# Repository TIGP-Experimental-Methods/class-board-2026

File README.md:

# class-board-2026

The teaching instrument for **Basic Skills for Experimentalists** (TIGP, 2026): one ESP32-S3 board (the ESP32-S3 is the microcontroller we use — a small computer on a chip, with WiFi) with three student-designed sections, a phone web app, and a Python client. The board is a small **NMR console**: a 2 mT field, a bottle of water, a pulse at 89 kHz, and the free induction decay that comes back turned into a spectrum on your phone.

| Folder | What | Who edits it |
|---|---|---|
| `hardware/` | KiCad project and library (KiCad is the free program we draw the schematic and lay out the printed circuit board in; the library is the set of symbols and footprints for our parts) | students in their zone (the region of the board that is theirs), instructor merges (brings their changes into the main line) |
| `firmware/` | PlatformIO project (Arduino, ESP32-S3) — the firmware is the program that runs on the microcontroller; PlatformIO is the tool that builds it and writes it onto the board | students, in the driver folders their instrument needs, under `src/blocks/` |
| `host/pwa/` | the phone app (plain HTML/JS, no build step) | students, in the panel files of those drivers, under `panels/` |
| `host/instrument.py` | Python command-line client (CLI) speaking the same protocol as the phone | instructor |

**The three sections of the board** (one design, made together in Workshop 2; each student added one section): **A — inputs and the NMR receiver** (the 8-channel 16-bit converter; the tuned coil, low-noise amplifier, blanking switch, I/Q mixer, IF filters and clock generator) · **B — signal generation, timing and the NMR transmitter** (±10 V outputs; the DDS synthesizer, reconstruction filter and power stage; TTL buffers, TRIG, the I²C expander) · **C — the front panel board** (the whole second board: the SMA field, the OLED, the LEDs, the TTL strip, the TX coil terminal and the Qwiic; the two isolated inputs; the module header with its 5 V buffer — seven outputs, MODULE OUT 1–7 plus a reserved spare pin, for driving opto-isolated modules outside the box). The instructor owns the base: the dev-board socket and the buses, the power entry and the rails, the external power input, the H-bridge and the polarizer switch.

**Firmware drivers** (the firmware calls each driver a *block*): `base` (dev board itself) · `b1_inputs` (ADS8688 8-ch ADC, analog-to-digital converter) · `b2_power` (rails) · `b3_outputs` (DAC8563 digital-to-analog converter + ±10 V) · `b4_switching` (7 module outputs, 2 isolated inputs) · `b5_dio_trig` (8 TTL out, 2 fast out, TRIG) · `nmr` (the console: pulse → free induction decay → spectrum). The drivers follow the sections: Section A `b1_inputs` and the receiver capture; Section B `b3_outputs` and `b5_dio_trig`; Section C `b4_switching`; `b2_power` is the instructor's. Protocol: [firmware/PROTOCOL.md](firmware/PROTOCOL.md).

Until the class board arrives everything runs in **SIM mode** on a bare Jinhua ESP32-S3 N16R8 dev board (the development board: the microcontroller on a small board with a USB connector and pins): each driver fakes its hardware, so the app, the chart and the alarms all work from Workshop 1.

**How this repository fits the course.** **Workshop 1: AI for experimentalists** is **Project 1** (a web app of your choice — a simulator or a game, built with the AI method) and **Project 2** (your own phone app that controls the ESP32 over WiFi). The firmware and app in this repository are **Step 1 of Project 2**: every student flashes them onto their own board first — a known working hardware baseline, which separates hardware problems from software problems — then builds their own app in its own repository, reading this code for the access point, the WebSocket and the LED. They stay the **fallback**: flash them again if your own build stalls and you have a working app on the phone today. In **Workshop 2: Designing printed circuit boards** we design the class board together in KiCad — one board for everyone. They are also the **base for Project 3** (from **Workshop 3: Firmware and basic mechanical design (PCB housing)**): your instrument — the firmware and the app that use the class board's capabilities, in a housing you design, presented on a great project website. You choose what instrument it is. The course ends with a project presentation and demonstration, 26–30 Oct.

## The student package (everything you need is in this repository — the project folder whose complete history git keeps, stored online on GitHub)

| What | Where |
|---|---|
| **Setup (before Workshop 1)** | [SETUP.md](SETUP.md) — paste the prompt from workbook ch. 0 into Claude Code and it installs the toolchain (the compiler and helper programs that turn source code into firmware) |
| **Workbook** — one chapter per workshop, each with a *between workshops* part ("Before the next workshop: complete the preparation, improve your apps, build and have fun."), the same text the tutor runs | [`workbook/`](workbook/README.md): [ch. 0](workbook/ch0-before-day-1.md) · [ch. 1](workbook/ch1-day-1-week-1.md) · [ch. 2](workbook/ch2-day-2-week-2.md) · [ch. 3](workbook/ch3-day-3-week-3.md) · [ch. 4](workbook/ch4-wrap-up-demo.md) · [A](workbook/chA-electronics-from-zero.md) · [B](workbook/chB-how-the-software-works.md) · [C cheat-sheets](workbook/chC-cheat-sheets.md) |
| **The section pages** (documentation of the class board's hardware) | [`workbook/blocks/`](workbook/blocks/): [A — inputs and the NMR receiver](workbook/blocks/a.md) · [B — signal generation, timing and the NMR transmitter](workbook/blocks/b.md) · [C — the front panel board](workbook/blocks/c.md) |
| **The tutor** (self-updating: fetches the latest guide and workbook from GitHub at the start of every session) | `/tutor L1` (etc.) in Claude Code — [`.claude/skills/tutor/`](.claude/skills/tutor/SKILL.md), rules in [`tutor/COURSE-GUIDE.md`](tutor/COURSE-GUIDE.md) |
| **Slides** | Workshop 1 as a PDF on the course site: https://tigp-experimental-methods.github.io/slides/W1-AI-for-experimentalists.pdf (Workshop 2 and 3 slides follow the same way; see [`slides/README.md`](slides/README.md)) |
| **Firmware + app** (Step 1 of Project 2 — the hardware baseline — and its fallback; the base of your Project 3 instrument) | `firmware/`, `host/` — flash it (write it onto the board over USB) in 5 commands below |
| **The class project wall** — one card per project (picture, title, student, two sentences, buttons *Open the app · Project site · Video · Code*), refreshed every minute, on the projector in class; every student pushes their own entries (workbook ch. 1, *Put it on the class project wall*). Project 3 — your instrument: its firmware, its app and the housing — is **one** repository, one project website and one card | https://tigp-experimental-methods.github.io/showcase-2026/ — repository https://github.com/TIGP-Experimental-Methods/showcase-2026 (its README documents the entry format) |
| **KiCad library package** | [`hardware/lib/`](hardware/lib/README.md) — project-local, nothing to unzip |
| **Reference repositories for Project 1** | https://github.com/TIGP-Experimental-Methods/pendulum-example (cart-pole) · https://github.com/TIGP-Experimental-Methods/csv-scope-example (CSV → scope lab tool) — options, or a fork (your own copy of one of them on GitHub) if your session stalls |
| **Course site** | https://tigp-experimental-methods.github.io/ |

## Flash in 5 commands (VS Code + PlatformIO)

Prerequisites: VS Code with the *PlatformIO IDE* extension (installs its own Python and `pio`), git, the dev board on a USB-C **data** cable plugged into the port marked *USB* (native USB, not *UART*).

```sh
git clone https://github.com/TIGP-Experimental-Methods/class-board-2026.git
cd class-board-2026/firmware
pio run -e esp32s3-sim -t upload        # 1st time: downloads the toolchain
pio run -e esp32s3-sim -t uploadfs      # copies host/pwa/ to the board's LittleFS (its file store)
pio device monitor                      # watch it boot; note the AP name
```

(In VS Code: PlatformIO sidebar → `esp32s3-sim` → *Upload*, then *Upload Filesystem Image*, then *Monitor*.)
If the upload cannot find a port: hold **BOOT**, tap **RST**, release BOOT, retry. Windows needs no driver for native USB.
If the upload says *"No serial data received"* (a factory-fresh board, USB ID `303A:4001`): hold **BOOT**, tap **RST**, release BOOT — the board comes back as `303A:1001` on a **new COM port**; `pio device list` again and flash to that port. Once only; the port also disappears and reappears at every reset, which is normal. All flashing and serial symptoms, and the secrets rule, are on one page: [workbook ch. C, §C.2](workbook/chC-cheat-sheets.md#c2-platformio).

## Open the app on your phone

1. The board's RGB LED turns **blue** = it is an access point (its own WiFi network, which your phone joins). Serial monitor prints `AP "instrument-XXXX" password "instrument"`.
2. On the phone join WiFi `instrument-XXXX`, password `instrument`.
3. Open **http://192.168.4.1** in the browser (type the `http://`; stay connected when the phone warns about no internet, mobile data off on Android). Tap *Red* on the Base tab: the LED changes. The chart plots `base.counter`; pick another key from the dropdown.
4. *Add to Home screen* gives an app icon. (Full "install" prompts need HTTPS, which the board does not have; the shortcut is enough.)

To use the lab WiFi instead: copy `firmware/include/secrets.h.example` to `secrets.h`, fill in SSID/password, and, if you want OTA (the update over WiFi), remove the `//` before `OTA_PASSWORD` and type a password of your own (left commented out, OTA stays off) — type the passwords into that file yourself, never into a Claude chat; the file is git-ignored (`git check-ignore -v firmware/include/secrets.h` prints a line) — and re-flash. For uploads over WiFi, copy `firmware/secrets.ini.example` to `firmware/secrets.ini` (git-ignored too), type the board's name and the same OTA password there, and run `pio run -d firmware -e esp32s3-ota -t upload`. The LED turns **green** and the board is at `http://instrument-XXXX.local` (mDNS: the board announces its own name on the local network, so no IP address is needed; `XXXX` is the same suffix as its access-point name, so several boards can share one network). If joining fails within 10 s it falls back to the AP.

## Python client

```sh
pip install -e host/            # or: uv pip install -e host/
instrument status
instrument send base led --args '{"r":0,"g":255,"b":0}'
instrument stream base.counter --seconds 5 --csv out.csv
instrument alarms list
```

It talks to `192.168.4.1` (the board's own access point); on a lab network give `--host instrument-XXXX.local` (XXXX = the last four hex digits of the MAC, printed in the boot log) or the IP address.

## Add a driver (Workshop 3, exercise E11)

1. Copy `firmware/src/blocks/template/` → the driver folder of the block your instrument needs, e.g. `firmware/src/blocks/b3_outputs/`. Rename the class and `name()` → `"b3"`.
2. Write the **SIM branch first**: `status()` returns plausible fake values; `handle()` accepts your commands. Flash; your tab appears with a generic key/value view.
3. Copy `host/pwa/panels/template.js` → `panels/b3.js`, set `id: 'b3'`, replace the example control. Add it to `PANELS` in `app.js`. `pio run -t uploadfs`; reload the phone.
4. Register the driver in `firmware/src/main.cpp` (one `registry.add(&b3)` line — the stub drivers are already registered, so you only replace the stub of the driver you are writing).
5. Fill the `#ifndef SIM` branches with the real driver using the pin constants in `firmware/include/pins.h`; the chip's protocol, the signal path and the limits are in [`docs/class-board-reference.md`](docs/class-board-reference.md) (one subsection per capability, with a minimal snippet).
6. Open a pull request (PR — a request to merge your changes into the shared project; someone reviews it first); CI (continuous integration — the automatic build GitHub runs on every pull request) builds both envs.

The rules: a driver talks only to its own hardware; all driver code runs from `loop()` (no tasks, no locks); every status key you show in the panel is one your `status()` emits.

## The housing (Workshop 3, Project 3)

`hardware/release/` holds the two board models (`class-board.stl`, `front-panel.stl` meshes and the STEP files, exported from the final KiCad boards with `kicad-cli`, keeping the connectors, LEDs and modules) and nothing else: the housing is yours to design, from the [housing brief](workbook/housing-brief.md) with Claude Code, in `docs/students/<name>/housing/`, starting by opening each board on its own in OpenSCAD; [chapter 3](workbook/ch3-day-3-week-3.md) §A.6 has the steps, and [SETUP.md](SETUP.md) Step 11 installs OpenSCAD and Bambu Studio.

## Add an alarm rule

Rules are data: `{block, key, op, threshold, action}`, evaluated 20× per second on the same status the app sees; they fire once when the condition becomes true.

- On the phone: **Alarms** tab → pick `b1.ai1`, `gt`, `9`, action `module 1 off` → *Add rule*.
- From a panel: `api.addAlarm({ block: 'b2', key: 'v5_raw', op: 'lt', threshold: 4.9, action: 'notify' })` (see `panels/template.js`).
- From Python: `instrument alarms add --block b1 --key ai1 --op gt --threshold 9 --action module:1:off`.

`action` is `notify` (toast on every phone, browser notification if allowed) or `module:<n>:on|off` (a module output on the front panel, Section C). Rules persist on the board in `/alarms.json`.

## Layout

```
firmware/
  platformio.ini            envs esp32s3 (real), esp32s3-sim (-DSIM=1), esp32s3-ota (esp32s3 over WiFi)
  secrets.ini.example       OTA upload template (board name, OTA password)
  include/pins.h            GPIO map of the boards as ordered (docs/class-board-reference.md §3)
  include/secrets.h.example WiFi and OTA password template
  scripts/copy_pwa.py       pre-build: host/pwa -> firmware/data
  src/main.cpp              WiFi, mDNS, OTA, HTTP + WebSocket, 20 Hz broadcast
  src/blocks/Block.h        the 5-method driver interface
  src/blocks/Registry.*     list of drivers
  src/blocks/base/          LED, counter, temperature
  src/blocks/template/      copy-me block
  src/blocks/b1_inputs/ … b5_dio_trig/
  src/alarm/AlarmEngine.*   rules, block "alarms"
  PROTOCOL.md
host/
  pwa/                      index.html app.js style.css sw.js manifest, panels/*.js
  instrument.py, pyproject.toml
hardware/sections/                the main board split four ways BY AREA for routing (A rear right, B front right, C front left, D rear left); README.md there
hardware/scripts/main_sections.py  areas / split / check / merge / report for the main-board areas
hardware/front-panel/sections/    the front panel split four ways for routing (A analog, B digital, C modules, D isolated + power); README.md there
hardware/scripts/panel_sections.py  split / check / merge the four sections back into one board
docs/
  references.md             papers (NMR at low field), datasheets of every part, tools and suppliers
  class-board-reference.md  THE BOARD, PIN BY PIN: connectors, links, every chip's protocol, levels, limits, firmware state, known defects (netlist-derived, 2026-10-08)
  references/               the two Creative-Commons papers as PDF
.github/workflows/build.yml  both envs + ruff on every push/PR
```

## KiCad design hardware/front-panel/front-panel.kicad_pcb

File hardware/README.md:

# TIGP class board 2026 — hardware (rev B, v0.7)

> **Revision names.** The boards ordered on 2026-10-05 and delivered in October 2026 are **rev B = v0.7** (the title block says v0.7; the panel's "rev C" text was a leftover). "Rev A" was the unbuilt v0.6 design of early September (`release/revA/`); no rev A board exists. The next revision, drawn after the order, is **V0.2** in [`V0.2/`](V0.2/) (`V0.2/CHANGES-V0.2.md`); it has not been ordered.
>
> **Superseded for the boards as ordered (2026-10-05) by [`../docs/class-board-reference.md`](../docs/class-board-reference.md).** This file describes the generated design of 17 September. The link pin assignments, the ADC channel map, the SMA count, the AGND/NT1 statements, the expansion header and the routing status below are out of date; the reference and [`docs/link-pinout.md`](docs/link-pinout.md) are derived from the netlist of the final design. The generator rules and the file map are still valid.

Two boards: the **main board** (ESP32-S3 dev-board carrier / lab instrument **and NMR console**, 4-layer
**180 × 100 mm**) and the **front panel** (**4-layer 180 × 100 mm**: 17 SMA on an 18 mm grid, OLED module socket,
3 LEDs, TTL screw strip, TX terminal, Qwiic, two isolated 5–24 V inputs, a 5 V TTL module header, three 2×20 links).
Specification: [`../10-Class-Board-Design-Brief.md`](../10-Class-Board-Design-Brief.md) v0.6 as amended by the v0.7
re-spec `notes/2026-09-13-nmr-respec-proposal.md` and the circuit design `notes/2026-09-13-v07-nmr-circuits.md` (both
in the course repo); build/verification contract: [`../prompt.md`](../prompt.md); working instructions for this
directory: [`AGENTS.md`](AGENTS.md).

## What changed on 2026-09-17 (v0.7d — course-repo Decision #58)

- **The four relays and all mains switching are gone** (D-53).  K401–K404 (JQC-3FF), the terminals J401–J404, the
  AO3400A drivers, the flyback diodes and the coil LEDs are deleted, the whole `b4_switching` sheet with them, and so
  are the `MAINS` / `MAINS1…4` net classes and every `mains_*` DRC rule.  Students who want to switch mains buy a
  ready-made opto-isolated relay module.
- **A module header replaces them.**  TCA9535 ports **P10–P13 and P15–P17 are MODULE OUT 1…7** (`MOD1…MOD7`; P14
  stays the 74HC74 `/CLR` of the NMR receiver).  They cross to the panel on **link J8 pins 19…31 odd**, where one
  **74AHCT541** on +5V_RAW buffers them to 5 V TTL, 47 Ω in series, into a **2×6 shrouded box header**
  (+5 V ×2, OUT1…8, GND ×2; **OUT 8 is a reserved spare**, J8 pin 33 not connected on the main board and held low
  on the panel).
- **The two isolated inputs moved to the front panel** (D-54), circuit unchanged: terminals J411/J412, the 1N4148W +
  220 Ω + MMBT5551 current source and the 6N137 stay together, and `OPTO_IN1/2` return over **J8 pins 35/37** to
  **GPIO16/17**.  The `ISO_IN` class, the 2.5 mm rule and the two keep-outs moved with them.
- **Student section C is the front-panel board** (D-55), a 4-layer project of its own.  The main board's former
  `ZONE_C` — power entry (`b2_power`) plus the coil switches (`c_switch`: +VEXT input, DRV8871 H-bridge, polarizer) —
  is the instructor's **`ZONE_INSTR`** (D-56); `ZONE_B` grew to take the rear-right strip (x 96–179.5, y 0.5–36).
- **The main board was re-placed (v0.7d):** 341 footprints, 0 tracks, the instructor block as one piece at
  **x 45–86** on the rear edge with J901 / J903 / J905 at x **51.0 / 62.7 / 76.9**, rotation 180.

## What v0.7 changed (2026-09-13)

- **Three student sections instead of five zones** (D-30): **A** = analog inputs + NMR receiver · **B** = analog
  outputs, digital I/O, timing + NMR transmitter · **C** = power, switching + coil switches.  *(Superseded
  2026-09-17, D-55: **C is now the front-panel board**, and the power entry and coil switches became the
  instructor's `ZONE_INSTR`.)*  The instructor keeps the base (dev-board socket, buses, expansion header, link).
  Ownership is enforced by the DRC rules `owner_A` / `owner_B` / **`owner_INSTR`** on each footprint's `Block` field.
- **An NMR console replaces the OPT conditioning chain** (D-32).  Target: proton NMR at **B0 = 2.1 mT,
  f_Larmor = 89.4 kHz**, thermal polarization, 60–250 mL of water, coil-detected; the architecture reaches ≥ 1 MHz by
  changing only the tank, the LNA gain and the drive level.  Three new blocks:
  - **NMR receiver** (section A, 7xx/9xx): Si5351A + 74HC74 Johnson counter for an exact quadrature LO, tuned tank
    with a crossed-diode limiter, OPA1656 LNA (gain 1000), DG419 blanking between the stages, a double-balanced I/Q
    commutating mixer on two TS5A23157 and IF difference amplifiers into **ADS8688 channels 7 and 8**.
  - **NMR transmitter** (section B, 8xx): AD9834 DDS on a 50.000 MHz clock, 3 MHz Butterworth reconstruction filter,
    OPA564 power stage running single-supply from `+VEXT` (15.9 V pp = a 417 µs 90° pulse), TX on the panel SMA and on
    a board-edge terminal.
  - **Power and coil switches** (section C, 9xx): an external 7–18 V / 5 A input with fuse, TVS and a P-FET
    (`+VEXT`), a DRV8871 field-cycling H-bridge, and a UCC27517 + AOD4184A polarizer switch with three flyback
    stuffing options (adiabatic transfer only).
- **Board 180 × 100 mm** (D-31): everything that stood at x ≥ 129 moved +40 mm, which bought 40 mm of rear edge for
  the three new terminals and a column for the transmitter.  The panel grows to 180 × 65 mm with a **3 × 5 SMA grid**;
  the new column carries TX, RX and SPARE, and link pins 37–40 became RX / AGND / TX / AGND (D-45, D-46).
  *(Panel geometry superseded: 180 × 100 mm, **4-layer**, 17 SMA at **18 mm** pitch — D-50/D-50a and Decisions
  #57/#58.)*
- **DIO1–8 and RELAY1–4 moved to a TCA9535 I²C expander** (D-40), which freed the 7 GPIO the NMR block needs and
  GPIO 4/6/7/15 for the expansion header.  *(Superseded 2026-09-17, D-53: the four relay ports P10–P13, plus
  P15–P17, are now MODULE OUT 1…7; the relays themselves are gone.)*

## Status

**Schematic and placement are generated and current; the main board is not routed.**

- Schematic: root + **9 sheets** (`opt_conditioning` gone in v0.7, **`b4_switching` gone in v0.7d**).
- PCB: **341 footprints** placed, the `ZONE_A` / `ZONE_B` / `ZONE_INSTR` / `ZONE_BASE` rule areas, the GND planes and
  the AGND pours written, **0 track segments and 0 vias** — routing is by hand (Workshop 2: students route their own
  section, the instructor routes the base, the rails and SPI).
- DRC: the custom rules **load** (the file is at the project root, D-48) and the `owner_A` / `owner_B` /
  `owner_INSTR` assertions pass on the generated placement.  A clean DRC on a routed board does not exist yet.
- Front panel: 4-layer 180 × 100 with the 18 mm SMA grid, the isolated inputs and the module header; it is
  **student section C** and is placed but not routed.  The released `release/revA/front-panel/` package is the
  **v0.6** panel and must be rebuilt.
- **No hardware has been built and nothing in `docs/bring-up.md` has been executed** (T-00…T-23 all pending).
  `docs/requirements.md` marks the honest status of every requirement.

## What is where

| Item | Path |
|---|---|
| Main-board project (KiCad 10) | `class-board.kicad_pro`, `class-board.kicad_sch`, `sheets/*.kicad_sch`, `class-board.kicad_pcb`, **`class-board.kicad_dru`** (the rules KiCad actually loads; `rules/class-board.kicad_dru` is the edit source) |
| Schematic sheets | `base_mcu`, `b1_inputs`, `b2_power`, `b3_outputs`, `b5_dio_trig`, **`nmr_rx`**, **`nmr_tx`**, **`c_switch`**, `front_panel_link` (`b4_switching` deleted 2026-09-17, D-53/D-54) |
| Sheet modules (v0.7) | `scripts/sheet_nmr_rx.py` (A), `scripts/sheet_nmr_tx.py` (B), `scripts/sheet_c_switch.py` (**instructor**) — each exposes `build(root_uuid) → Sheet` for `gen_sch.py` and a `PLACEMENT` dict for `gen_pcb.py` |
| Front-panel project | `front-panel/front-panel.kicad_pro/.kicad_sch/.kicad_pcb/.kicad_dru` (generated by `scripts/gen_panel.py`) — **4-layer, and this is student section C** |
| Project-local library | `lib/class_board.kicad_sym`, `lib/class_board.pretty/`, `lib/class_board.3dshapes/` (both projects use it through their `sym-lib-table` / `fp-lib-table`) |
| Release package | `release/<rev>/main-board/`, `release/<rev>/front-panel/` (Gerbers, drill, BOM, CPL, PDFs, SVG/PNG, STEP, reports, hashes) — only the v0.6 front panel exists so far |
| Design record | `docs/design-decisions.md` (D-01…D-57), `docs/requirements.md` (R-01…R-47), `docs/design-review.md` (floorplan, grounding, PDN, block risks incl. §5.7 NMR, manufacturing, findings F-01…F-23, layout log), `docs/bring-up.md` (T-00…T-23), `docs/student-deletions.md` |
| Student copies | `student/<sheet>_gapped.kicad_sch` (+ `.kicad_pro`, lib tables): section A = `b1_inputs` + `nmr_rx`, B = `b3_outputs` + `b5_dio_trig` + `nmr_tx`.  **Section C is the whole front-panel project**, unrouted, not a gapped sheet (D-55).  `b2_power` and `c_switch` are **not** gapped — they are the instructor's `ZONE_INSTR` |
| Generators | `scripts/` — see `AGENTS.md`; the schematic and the placement are generated, edit the scripts |

## Reference-designator ranges

| Range | Block |
|---|---|
| 1xx | B1 analog inputs (ADS8688 and the eight input networks) — section A |
| 2xx | B2 power entry and rails — **instructor (`ZONE_INSTR`)** |
| 3xx | B3 analog outputs (DAC8563, OPA2192) — section B |
| 4xx | former B4 relays and isolated inputs.  The relays are **deleted**; the isolated inputs (J411/J412 and their parts) and the new module-header block (U410, C410, R481–R489, J40) are on the **front panel** — section C |
| 5xx | B5 digital I/O, fast outputs, TRIG, TCXO option — section B |
| 6xx | former OPT conditioning chain — **deleted in v0.7** |
| **7xx** | **clocks and receiver**: Si5351A, crystal, 74HC74 divider, tank, limiter, LNA, blanking — section A |
| **8xx** | **DDS and transmitter**: AD9834, reconstruction filter, OPA564 power stage, TX terminal — section B |
| **9xx** | **mixer, IF, coil switches and external power**: mixer switches and IF amplifiers (section A); H-bridge, polarizer switch, +VEXT input (**instructor, `ZONE_INSTR`**) |

## Order / assembly configuration the package supports

- **Main board: 7 boards, 180 × 100 mm, 4-layer** JLC04161H-7628 stack-up, 1.6 mm — **5 assembled + 2 bare**;
  Economic PCBA, **top side only** (all parts are on F.Cu), SMD + THT; DNP parts (TCXO option, the SMBJ20A fast-dump
  clamp, the I²C pull-ups duplicated on the RX sheet, the flag pull-ups) are excluded from BOM and CPL.
- **Front panel: 6 boards, 180 × 100 mm, 4-layer**, 1.6 mm, all assembled; every part on the outer face except the
  three 2×20 male link headers on the inner face (hand-soldered; the main board carries the female sockets on its back, Decision #62) — the panel is single-sided for
  assembly apart from those headers (Decision #58 d).
- BOM columns *Comment, Designator, Footprint, LCSC Part #*; CPL *Designator, Mid X, Mid Y, Layer, Rotation*, origin
  bottom-left, mm, y up.  **Check the component rotations in JLC's upload preview** — still not done (finding F-13),
  and v0.7 adds exposed-pad and fine-pitch packages (HSOP-20 PowerPAD, SO-8-EP, TSSOP-24, MSOP-10, TO-252).
- The line count and cost below are the 2026-09-13 figures and **must be recounted after v0.7d**: the relays, their
  terminals, drivers, diodes and LEDs came off the main board and the module-header parts (74AHCT541, box header,
  47 Ω, 10 k) went onto the panel.  As counted then: 97 distinct LCSC lines (v0.6: 44), estimated order cost
  ≈ US$720 (v0.6 ≈ US$500).  **Read Basic/Preferred/Extended by hand in the JLC BOM tool before ordering** (D-49):
  the ADI/TI/Vishay silicon is certainly Extended at ≈ US$3 each per order.  Order cutoff: **Mon 28 Sep 2 pm**.

## Generation rule (v0.7) — the PCB becomes the master

UUIDs are deterministic (`uuid5`, D-47), so regenerating the schematic produces a byte-identical file for identical
inputs and every change diffs.  Therefore:

> **Regenerate the schematic freely.  Never regenerate the PCB once hand routing has started** — from that moment
> `class-board.kicad_pcb` is the hand-edited master and `scripts/gen_pcb.py` is only the placement reference.
> Running it would delete every track.

## Interface summary

- Rails: +5V_RAW (USB-C / jack, LM66100 ORing) → +3V3 (AMS1117); ±12 V isolated modules → +5VA (78L05);
  **+3V3A** (ferrite-filtered, for the Johnson divider and the mixer switches); **+VEXT** (external 7–18 V input, for
  the OPA564, the DRV8871 and the polarizer gate driver only).  AGND ↔ GND only at the net tie NT1.  L2 and L3 are
  unbroken GND planes (D-01).
- ADC channel map **on the ordered boards (netlist audit 2026-09-30, firmware `kAinOfAi`, `boards/class-board.json`):
  AI1→AIN_1, AI2→AIN_0, AI3→AIN_7, AI4→AIN_6, AI5→AIN_5, AI6→AIN_4, AI7→AIN_3, AI8→AIN_2.** The D-19 order
  (AI1→AIN_6 … AI8→AIN_5) was the generated design's and is no longer true. **Channels 7 and 8 (AIN_3/AIN_2) carry the
  mixer I and Q** when J14/J15 are on 2-3; 1-2 gives the panel SMA per channel.
- GPIO v0.7d (D-40, D-53, D-54; root sheet carries the table): 41 DDS_FSYNC · 42 DDS_PSEL · 40 TX_EN · 8 RX_BLANK ·
  9/14 HB_IN1/2 · 47 FET_GATE · **16/17 OPTO_IN1/2 (the isolated inputs, now on the panel, over J8 pins 35/37)**;
  DIO1–8 = TCA9535 P0.0–P0.7, **MODULE OUT 1…7 = P1.0–P1.3 and P1.5–P1.7** (P1.4 = the NMR receiver's 74HC74 `/CLR`);
  GPIO 4/6/7/15 free to the expansion header; GPIO 3 unused.  I²C: OLED 0x3C, TCA9535 0x20, Si5351A 0x60.
- Link J6/J1: pinout per brief 7.8 with **pins 37–40 = RX / AGND / TX / AGND** (D-45); the panel's back-side header
  has pairwise-swapped pad numbers (D-25), asserted geometrically by `gen_panel.py`.  **J8 (panel J3)** carries the
  rails, the free GPIO, **MODULE OUT 1…7 on pins 19…31 odd** (pin 33 = the reserved OUT 8, not connected) and
  **OPTO_IN1/2 on pins 35/37**, each with GND on the adjacent even pin.
- **Power-on order: USB first, then the +VEXT bench supply** (the OPA564 requires VDIG before V+, D-35).
- Open items to close with hardware in hand: dev-board socket row spacing 25.4 mm (D-12), panel header mating height
  (D-25), the land patterns of the new packages (F-12), the CPL rotations (F-13).

## Release status

No main-board release exists.  `release/revA/verification.json` covers the v0.6 front panel only.  A v0.7 release
requires: hand routing finished, DRC 0 errors / 0 unconnected with zones refilled, the angle audit clean, the BOM
without missing LCSC numbers, `scripts/release.py` fixed to find `kicad-cli` (F-15), and the JLC rotation preview
checked.

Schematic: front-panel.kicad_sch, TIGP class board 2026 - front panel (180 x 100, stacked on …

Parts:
C401, C402, C410: 100nF; C_0603_1608Metric; MPN CC0603KRX7R9BB104; LCSC C14663
D1, D2, D3: GREEN; LED0805-R-RD; MPN KT-0805G; LCSC C2297
D421, D422: 1N4148W; SOD-123F_L2.7-W1.6-LS3.8-RD; MPN 1N4148W; LCSC C81598
FID1, FID2: Fiducial; Fiducial_1mm_Mask2mm
H1, H2, H3, H4: M3; MountingHole_3.2mm_M3
J1, J2, J3: Conn_02x20_Odd_Even; PinHeader_2x20_P2.54mm_Vertical
J10, J11, J12, J13, J14, J15, J16, J17, J18, J19, J20, J21, J22, J23, J24, J25: SMA; SMA-TH_BWSMA-KE-Z001; MPN BWSMA-KE-Z001; LCSC C496549
J30: OLED 0.96in module on 1x4 socket 8.5 mm; OLED-0.96in-4P-module-socket; MPN PZ254-1-04-Z-8.5; LCSC C2894927
J31: KF128-2.54-10P; CONN-TH_10P-P2.54_KF128-2.54-10P; MPN KF128-2.54-10P; LCSC C474928
J32: KF128-5.0-2P; CONN-TH_P5.00_KF128-5.0-2P; MPN KF128-5.0-2P; LCSC C474950
J33: Qwiic (vertical); CONN-SMD_BM04B-SRSS-TB; MPN XY-BM04B-SRSS-TB; LCSC C51940129
J40: Module header 2x6 (shrouded); IDC-Header_2x06_P2.54mm_Vertical; MPN BH254V-12P; LCSC C48687626
J411, J412: KF301-5.0-2P; CONN-TH_P5.00_KF301-5.0-2P; MPN KF301-5.0-2P; LCSC C474881
Q411, Q412, Q421, Q422: MMBT5551; SOT-23-3_L2.9-W1.6-P1.90-LS2.8-BR; MPN MMBT5551; LCSC C2145
R1, R2, R3, R461, R462, R471, R472: 1k; R_0603_1608Metric; MPN 0603WAF1001T5E; LCSC C21190
R431, R432: 220; R_0603_1608Metric; MPN 0603WAF2200T5E; LCSC C22962
R441, R442, R491, R492, R493, R494, R495, R496, R497, R498: 10k; R_0603_1608Metric; MPN 0603WAF1002T5E; LCSC C25804
R451, R452: 100; R_0603_1608Metric; MPN 0603WAF1000T5E; LCSC C22775
R481, R482, R483, R484, R485, R486, R487, R488: 47; R_0603_1608Metric; MPN 0603WAF470JT5E; LCSC C23182
U401, U402: 6N137S-TA1-L; SOP-8_L9.8-W6.6-P2.54-LS10.3-BL; MPN 6N137S-TA1-L; LCSC C92651
U410: SN74AHCT541PWR; TSSOP-20_L6.5-W4.4-P0.65-LS6.4-BL; MPN SN74AHCT541PWR; LCSC C50989

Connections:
/AI1: J1.40, J16.5 (SIG)
/AI2: J1.38, J17.5 (SIG)
/AI3: J1.36, J18.5 (SIG)
/AI4: J1.34, J19.5 (SIG)
/AI5: J1.30, J22.5 (SIG)
/AI6: J1.28, J23.5 (SIG)
/AI7: J1.26, J24.5 (SIG)
/AI8: J1.24, J25.5 (SIG)
/AO1: J1.18, J10.5 (SIG)
/AO2: J1.16, J11.5 (SIG)
/AUX: J1.22, J14.5 (SIG)
/FASTTTL1: J2.39, J15.5 (SIG)
/FASTTTL2: J2.37, J21.5 (SIG)
/I2C_SCL: J2.31, J30.3 (SCL), J33.4 (SCL)
/I2C_SDA: J2.33, J30.4 (SDA), J33.3 (SDA)
/ISO1_B: Q411.1 (B), Q421.3 (C), R441.2
/ISO1_C: Q411.3 (C), R431.2
/ISO1_E: Q411.2 (E), Q421.1 (B), R451.1, R461.1
/ISO1_IN+: D421.2 (A), J411.1
/ISO1_IN-: J411.2, U401.3 (CATHODE)
/ISO1_LEDA: Q421.2 (E), R451.2, R461.2, U401.2 (ANODE)
/ISO1_NODE: D421.1 (K), R431.1, R441.1
/ISO2_B: Q412.1 (B), Q422.3 (C), R442.2
/ISO2_C: Q412.3 (C), R432.2
/ISO2_E: Q412.2 (E), Q422.1 (B), R452.1, R462.1
/ISO2_IN+: D422.2 (A), J412.1
/ISO2_IN-: J412.2, U402.3 (CATHODE)
/ISO2_LEDA: Q422.2 (E), R452.2, R462.2, U402.2 (ANODE)
/ISO2_NODE: D422.1 (K), R432.1, R442.1
/LED_ACT: J2.23, R3.1
/LED_ACT_A: D3.1 (K), R3.2
/LED_PWR_A: D1.1 (K), R1.2
/LED_WIFI: J2.25, R2.1
/LED_WIFI_A: D2.1 (K), R2.2
/MOD1: J3.23, R491.1, U410.2 (A1)
/MOD2: J3.25, R492.1, U410.3 (A2)
/MOD3: J3.27, R493.1, U410.4 (A3)
/MOD4: J3.29, R494.1, U410.5 (A4)
/MOD5: J3.31, R495.1, U410.6 (A5)
/MOD6: J3.33, R496.1, U410.7 (A6)
/MOD7: J3.35, R497.1, U410.8 (A7)
/MOD8: R498.1, U410.9 (A8)
/MODOUT1: J40.3, R481.2
/MODOUT2: J40.4, R482.2
/MODOUT3: J40.5, R483.2
/MODOUT4: J40.6, R484.2
/MODOUT5: J40.7, R485.2
/MODOUT6: J40.8, R486.2
/MODOUT7: J40.9, R487.2
/MODOUT8: J40.10, R488.2
/MODY1: R481.1, U410.18 (Y1)
/MODY2: R482.1, U410.17 (Y2)
/MODY3: R483.1, U410.16 (Y3)
/MODY4: R484.1, U410.15 (Y4)
/MODY5: R485.1, U410.14 (Y5)
/MODY6: R486.1, U410.13 (Y6)
/MODY7: R487.1, U410.12 (Y7)
/MODY8: R488.1, U410.11 (Y8)
/OPTO_IN1: J3.15, R471.2, U401.6 (VO)
/OPTO_IN2: J3.17, R472.2, U402.6 (VO)
/RX: J1.20, J13.5 (SIG)
/TRIG_5V: J2.35, J12.5 (SIG)
/TTL1: J2.15, J31.1
/TTL2: J2.13, J31.2
/TTL3: J2.11, J31.3
/TTL4: J2.9, J31.4
/TTL5: J2.7, J31.5
/TTL6: J2.5, J31.6
/TTL7: J2.3, J31.7
/TTL8: J2.1, J31.8
/TX: J1.10, J1.12, J20.5 (SIG), J32.1

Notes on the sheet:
TTL1..8 out (5 V, 1 kohm series on the main board) + 2 x GND
SPARE SMA: shield on AGND, centre pin on TP1 only (no link pin)
GPIO6
2026-10-01: U401/U402 6N137 VCC and VE now on +5V_RAW (spec 4.5-5.5 V); the output pull-ups R471/R472 stay on +3V3 (GPIO16/17 are not 5 V tolerant). J1 pin 20 = RX (SMA J13, receiver tank), pin 22 = AUX (SMA J14, R715 option), matching the main board.
AO1/AO2: +-10 V, 49.9 ohm back-terminated. AI1..AI8: +-10 V, 1 kohm series on the main board. TRIG: 5 V into open circuit, about 2.4 V into 50 ohm. FAST1/FAST2 = the main-board nets FASTTTL1 / FASTTTL2.
panel label: AI5 (43, 61) mm
R491..R498: 10 k pull-down on every module line (the expander boots with its ports as inputs). MOD8 = J3 pin 33 is a reserved spare with no main-board driver at all.
panel label: AI6 (61, 61) mm
ISOLATED INPUTS - 6N137 channels moved to the panel; ISO_IN net class, 2.5 mm to everything else
J1 - analog (inner face): mates J6, the analog header
Panel coordinates are mirrored in x against the main board (panel x = 180 - main x, panel y = main y), because the panel is drawn from its OUTER face. The main board's REAR edge is therefore the panel's TOP edge.
panel label: TRIG (79, 25) mm
panel label: AI2 (61, 43) mm
Qwiic (vertical): sensor from the front; shell pads on GND
panel label: ACT
GPIO7
H1-H4: M3, same pattern as the main board (stand-offs). The OLED module's M2 holes are part of J30.
Pins marked spare are not connected on the main board and are left unconnected here. SPARE (the 18th SMA position is empty; the fitted SPARE SMA) has its shield on AGND and its centre pin on TP1 only.
100 nF at the 541's VCC pin
J1xtra - digital (inner face): mates J7, the digital header
Series 1N4148W (reverse blocking) -> 220 R -> Q1 pass transistor with Q2 sensing 0.65 V across Rs (100 R || 1 k = 91 R): LED current about 6.5-7 mA from 5 V to 24 V (the 6N137 needs 5-15 mA). At 24 V Q1 dissipates about 125 mW (MMBT5551 is rated 300 mW).
panel label: AO1 (43, 25) mm
MODULE HEADER - eight 5 V TTL outputs for an off-board relay / H-bridge module
GPIO44
panel x = 12 mm (main board x = 168 mm)
MOD8
Both output enables are tied to GND, so the buffer is always on: the module lines are held low by the expander's own power-up state, not by a 3-state.
panel label: AI8 (97, 61) mm
0.96 in I2C OLED (0x3C) on an 8.5 mm vertical socket: the module lies flat on four M2 stand-offs (holes in the footprint)
TX coil terminal, beside the TX SMA (kept: user 2026-09-16)
panel label: AI4 (97, 43) mm
The isolated half of each channel keeps 2.5 mm to every other net on every layer (ISO_IN class) and no pour of any net runs under it - see front-panel.kicad_dru and the two ISO keep-outs in the PCB.
17 SMA on a 20 mm grid (3 x 6, the 18th position is empty). Shields on AGND; the panel copper is AGND on both layers.
panel label: MODULE OUT 1..7 5 V TTL (8 = spare) relay / H-bridge modules
MOD1..8 come from the main board's TCA9535 expander at 3.3 V on J3 pins 19..33. ONE 74AHCT541 on +5V_RAW lifts them to 5 V TTL (AHCT thresholds accept 3.3 V); 47 ohm in series limits a shorted output and damps the ribbon cable.
panel label: AUX (97, 25) mm
J412 on the panel's LEFT EDGE: 1 = IN+, 2 = IN- (5-24 V DC, isolated, 5 kVrms). Wires enter off the edge.
GPIO43
PWR is +3V3 from the link (1 kohm -> about 1 mA); WIFI / ACT come from GPIO43 / GPIO44 through JP1 / JP2 on the main board.
panel label: TX (115, 25) mm

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
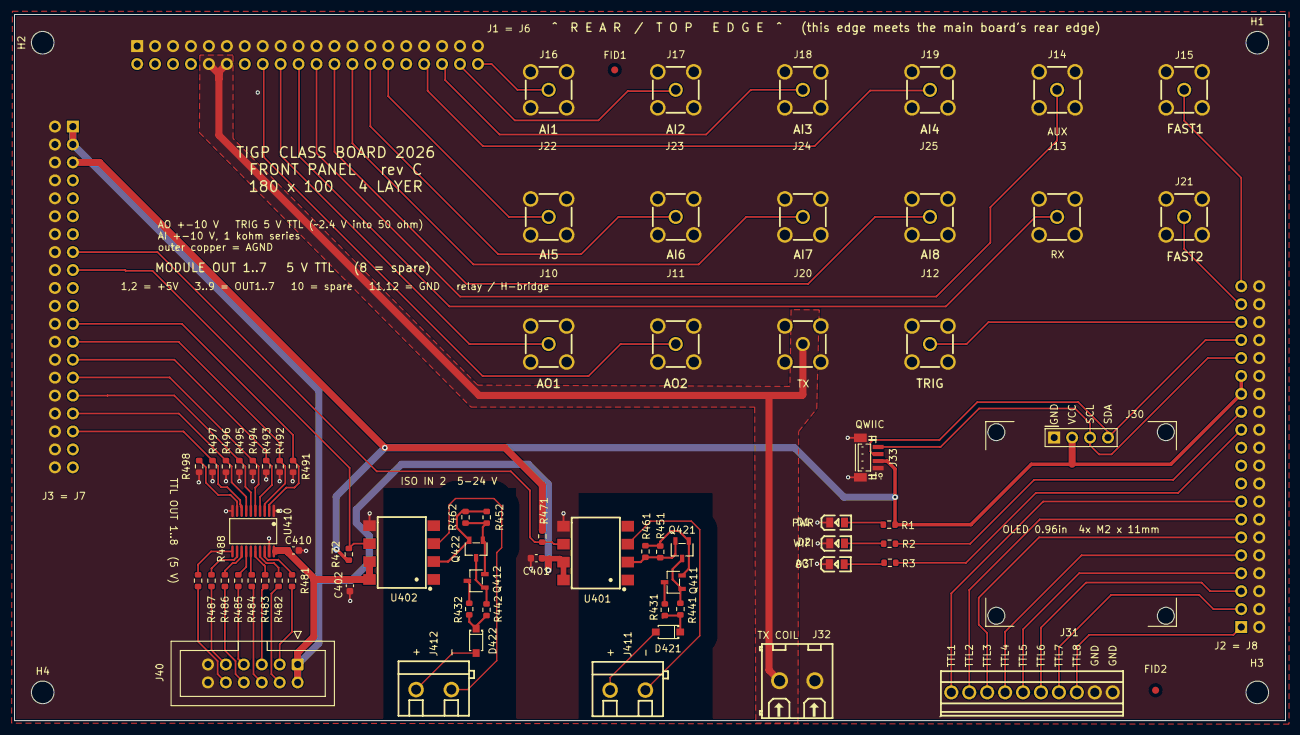
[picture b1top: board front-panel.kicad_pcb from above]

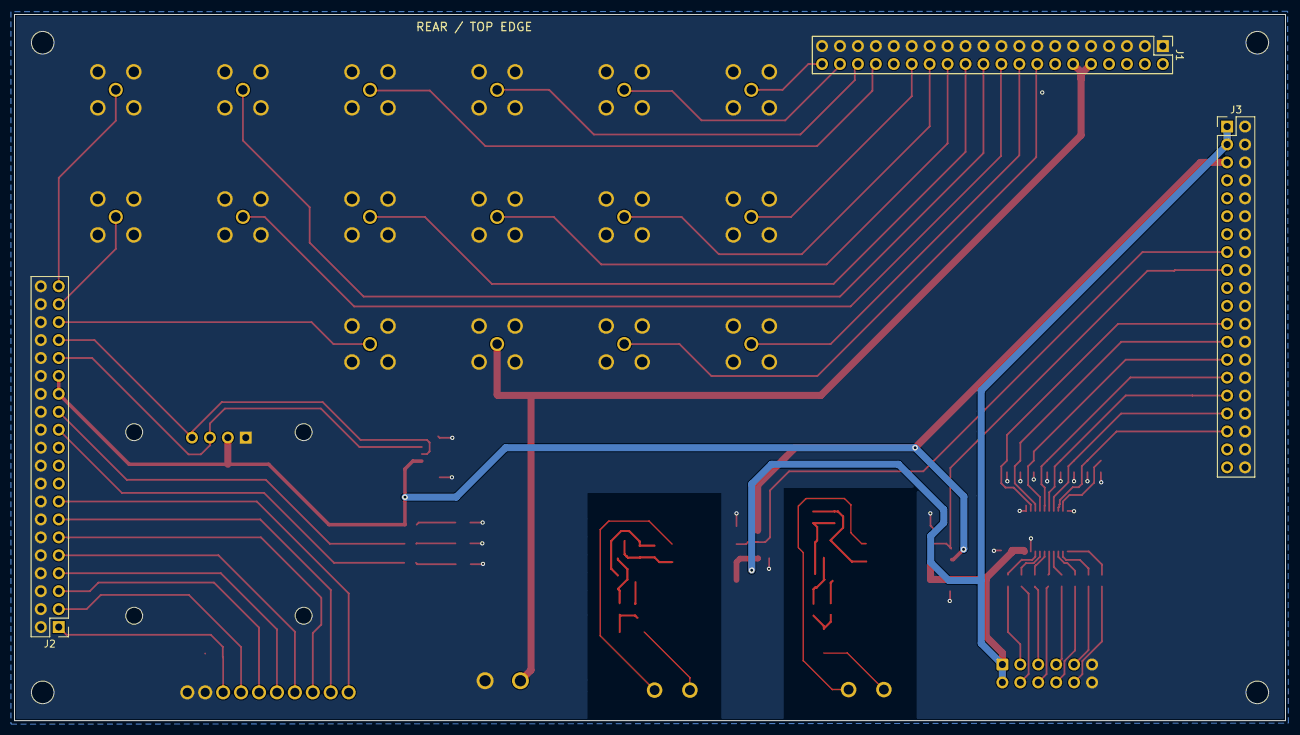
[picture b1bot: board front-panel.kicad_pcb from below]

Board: 4 copper layers, 180.0 x 100.0 mm, 76 parts (3 on the bottom side), 74 nets.

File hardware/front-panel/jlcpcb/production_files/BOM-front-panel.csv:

Comment,Designator,Footprint,LCSC,Quantity
100nF,"C401,C402,C410",C_0603_1608Metric,C14663,3
1k,"R1,R2,R3,R461,R462,R471,R472",R_0603_1608Metric,C21190,7
MMBT5551,"Q411,Q412,Q421,Q422",SOT-23-3_L2.9-W1.6-P1.90-LS2.8-BR,C2145,4
100,"R451,R452",R_0603_1608Metric,C22775,2
220,"R431,R432",R_0603_1608Metric,C22962,2
GREEN,"D1,D2,D3",LED0805-R-RD,C2297,3
47,"R481,R482,R483,R484,R485,R486,R487,R488",R_0603_1608Metric,C23182,8
10k,"R441,R442,R491,R492,R493,R494,R495,R496,R497,R498",R_0603_1608Metric,C25804,10
OLED 0.96in module on 1x4 socket 8.5 mm,J30,OLED-0.96in-4P-module-socket,C2894927,1
KF301-5.0-2P,"J411,J412",CONN-TH_P5.00_KF301-5.0-2P,C474881,2
KF128-2.54-10P,J31,CONN-TH_10P-P2.54_KF128-2.54-10P,C474928,1
KF128-5.0-2P,J32,CONN-TH_P5.00_KF128-5.0-2P,C474950,1
Module header 2x6 (shrouded),J40,IDC-Header_2x06_P2.54mm_Vertical,C48687626,1
SMA,"J10,J11,J12,J13,J14,J15,J16,J17,J18,J19,J20,J21,J22,J23,J24,J25",SMA-TH_BWSMA-KE-Z001,C496549,16
SN74AHCT541PWR,U410,TSSOP-20_L6.5-W4.4-P0.65-LS6.4-BL,C50989,1
Qwiic (vertical),J33,CONN-SMD_BM04B-SRSS-TB,C51940129,1
1N4148W,"D421,D422",SOD-123F_L2.7-W1.6-LS3.8-RD,C81598,2
6N137S-TA1-L,"U401,U402",SOP-8_L9.8-W6.6-P2.54-LS10.3-BL,C92651,2

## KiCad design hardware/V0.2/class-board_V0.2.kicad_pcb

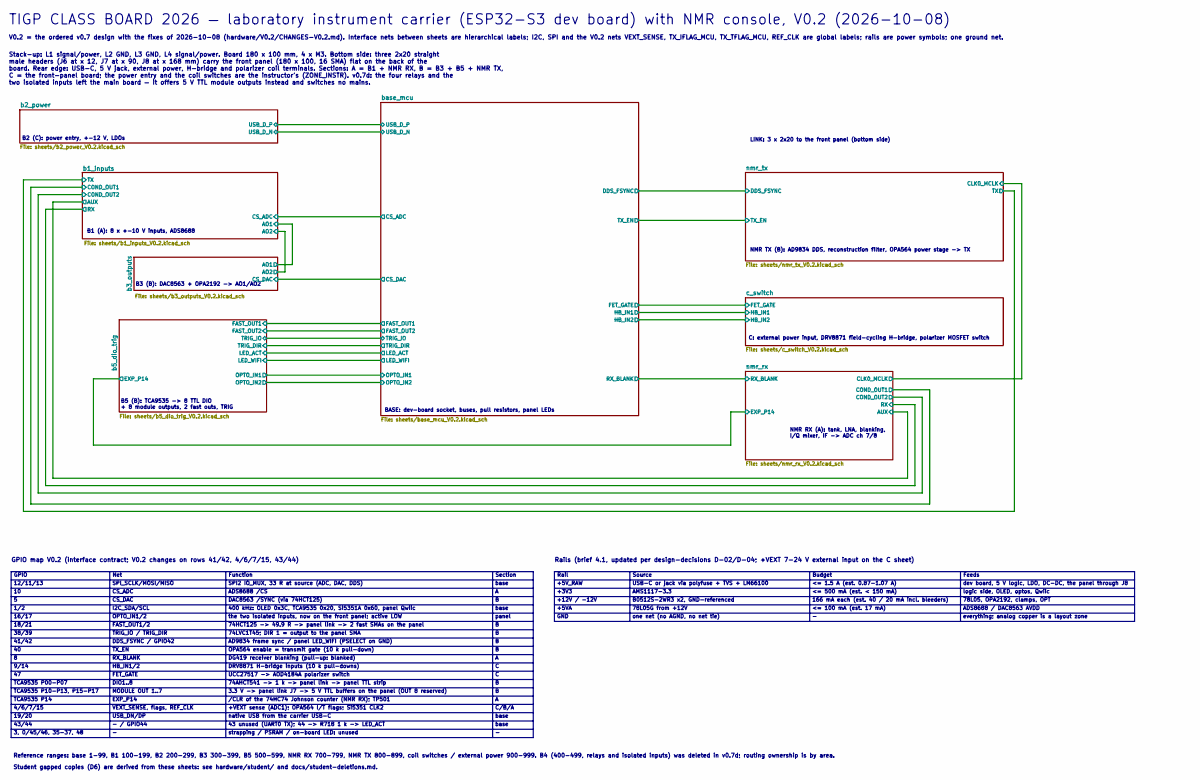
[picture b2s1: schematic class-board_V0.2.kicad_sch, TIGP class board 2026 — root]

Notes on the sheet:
dev board, 5 V logic, LDO, DC-DC, the panel through J8
Function
74AHCT541 -> 1 k -> panel link -> panel TTL strip
+3V3
9/14
DAC8563 /SYNC (via 74HCT125)
DG419 receiver blanking (pull-up: blanked)
DRV8871 H-bridge inputs (10 k pull-downs)
HB_IN1/2
LINK: 3 x 2x20 to the front panel (bottom side)
16/17
SPI_SCLK/MOSI/MISO
/CLR of the 74HC74 Johnson counter (NMR RX); TP501
ADS8688 / DAC8563 AVDD
NMR RX (A): tank, LNA, blanking, I/Q mixer, IF -> ADC ch 7/8
166 mA each (est. 40 / 20 mA incl. bleeders)
MODULE OUT 1..7
panel
SPI2 IO_MUX, 33 R at source (ADC, DAC, DDS)
+5V_RAW
<= 500 mA (est. < 150 mA)
OPA564 enable = transmit gate (10 k pull-down)
B1 (A): 8 x +-10 V inputs, ADS8688
74LVC1T45; DIR 1 = output to the panel SMA
18/21
Feeds
Budget
+12V / -12V
19/20
Rail
base
4/6/7/15
78L05, OPA2192, clamps, OPT
AMS1117-3.3
B3 (B): DAC8563 + OPA2192 -> AO1/AO2
TCA9535 P00-P07
the two isolated inputs, now on the front panel; active LOW
CS_DAC
OPTO_IN1/2
UCC27517 -> AOD4184A polarizer switch

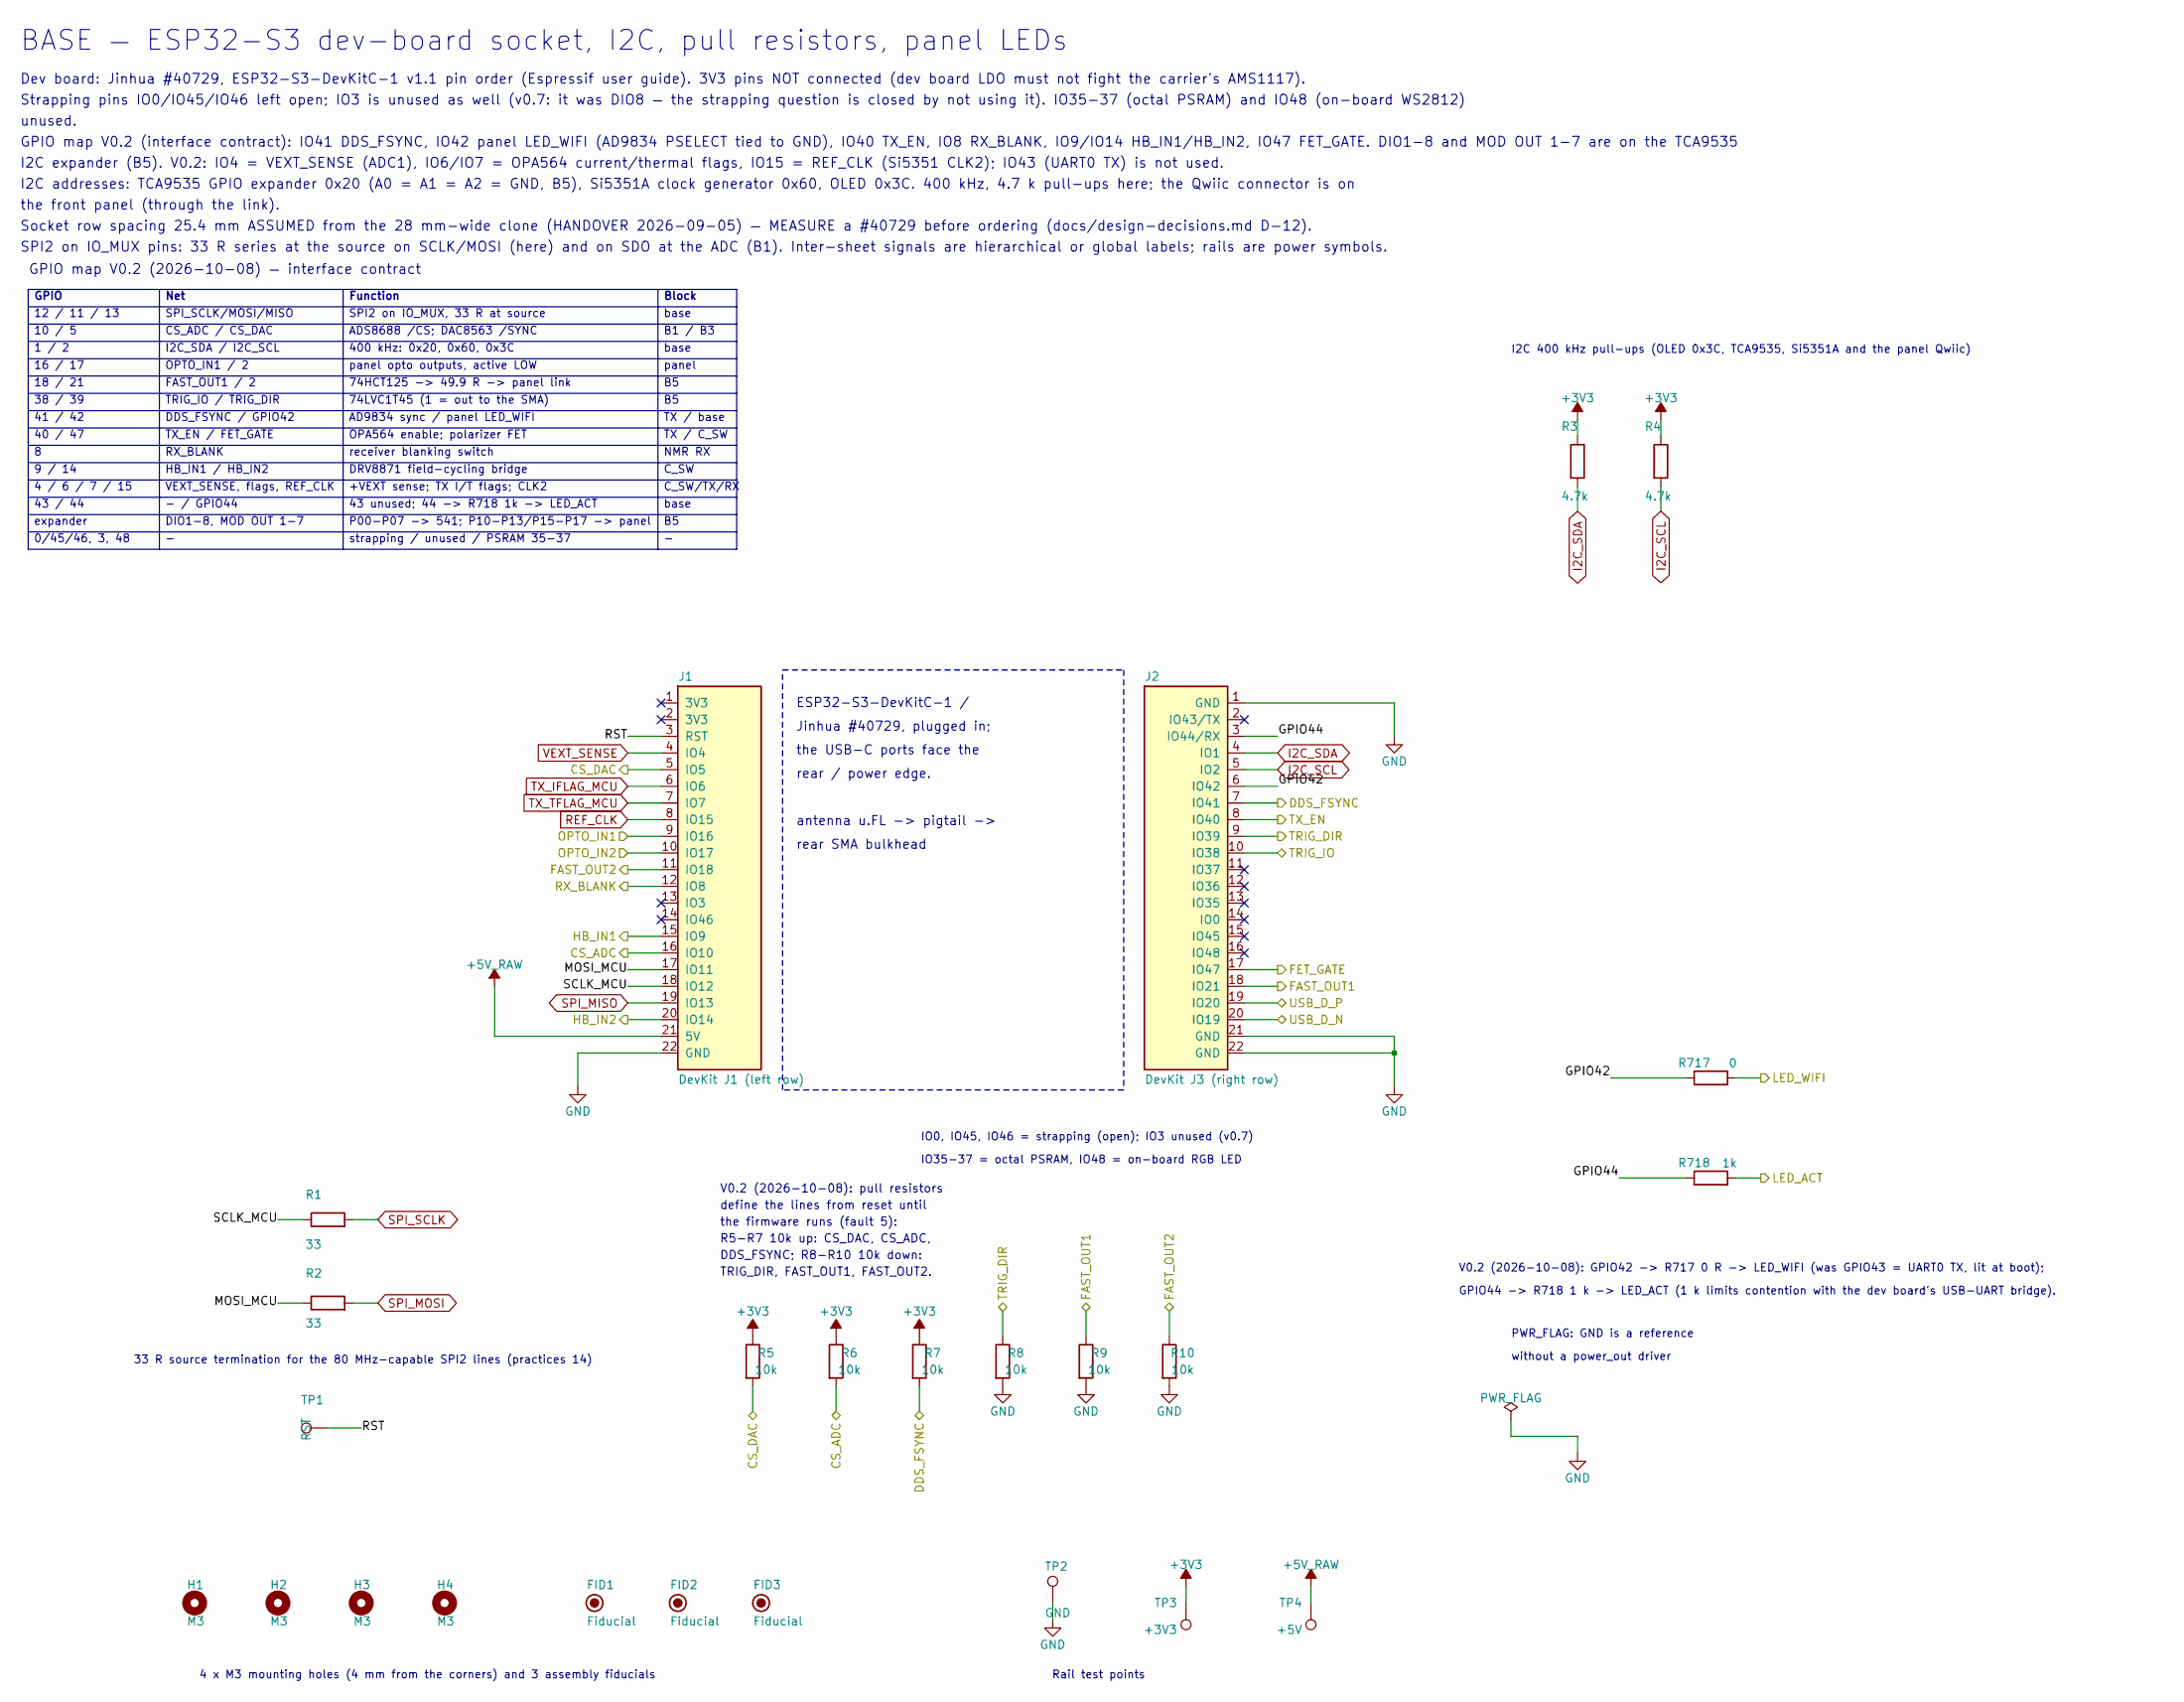
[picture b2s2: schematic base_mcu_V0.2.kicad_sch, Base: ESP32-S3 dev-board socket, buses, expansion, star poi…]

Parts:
FID1, FID2, FID3: Fiducial; Fiducial_1mm_Mask2mm
H1, H2, H3, H4: M3; MountingHole_3.2mm_M3
J1: DevKit J1 (left row); HDR-TH_22P-P2.54-V-F; MPN ZX-PM2.54-1-22PY; LCSC C7499337
J2: DevKit J3 (right row); HDR-TH_22P-P2.54-V-F; MPN ZX-PM2.54-1-22PY; LCSC C7499337
R1, R2: 33; R_0603_1608Metric; MPN 0603WAF330JT5E; LCSC C23140
R3, R4: 4.7k; R_0603_1608Metric; MPN 0603WAF4701T5E; LCSC C23162
R5, R6, R7, R8, R9, R10: 10k; R_0603_1608Metric; MPN 0603WAF1002T5E; JLC_CLASS Basic
R717: 0; R_0805_2012Metric_Pad1.20x1.40mm_HandSolder; LCSC C17477
R718: 1k; R_0805_2012Metric_Pad1.20x1.40mm_HandSolder; MPN 0805W8F1001T5E; LCSC C17513
TP1: RST; TestPoint_Pad_D1.5mm
TP2: GND; TestPoint_Pad_D1.5mm
TP3: +3V3; TestPoint_Pad_D1.5mm
TP4: +5V; TestPoint_Pad_D1.5mm

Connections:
+3V3: R3.1, R4.1, R5.1, R6.1, R7.1, TP3.1 (1_1); also elsewhere on the board
/b1_inputs/CS_ADC: J1.16 (IO10), R6.2; also elsewhere on the board
/b2_power/USB_D_N: J2.20 (IO19); also elsewhere on the board
/b2_power/USB_D_P: J2.19 (IO20); also elsewhere on the board
/b3_outputs/CS_DAC: J1.5 (IO5), R5.2; also elsewhere on the board
/b5_dio_trig/FAST_OUT1: J2.18 (IO21), R9.1; also elsewhere on the board
/b5_dio_trig/FAST_OUT2: J1.11 (IO18), R10.1; also elsewhere on the board
/b5_dio_trig/LED_ACT: R718.2; also elsewhere on the board
/b5_dio_trig/LED_WIFI: R717.2; also elsewhere on the board
/b5_dio_trig/OPTO_IN1: J1.9 (IO16); also elsewhere on the board
/b5_dio_trig/OPTO_IN2: J1.10 (IO17); also elsewhere on the board
/b5_dio_trig/TRIG_DIR: J2.9 (IO39), R8.1; also elsewhere on the board
/b5_dio_trig/TRIG_IO: J2.10 (IO38); also elsewhere on the board
/base_mcu/DDS_FSYNC: J2.7 (IO41), R7.2; also elsewhere on the board
/base_mcu/FET_GATE: J2.17 (IO47); also elsewhere on the board
/base_mcu/GPIO42: J2.6 (IO42), R717.1
/base_mcu/GPIO44: J2.3 (IO44/RX), R718.1
/base_mcu/HB_IN1: J1.15 (IO9); also elsewhere on the board
/base_mcu/HB_IN2: J1.20 (IO14); also elsewhere on the board
/base_mcu/MOSI_MCU: J1.17 (IO11), R2.1
/base_mcu/RST: J1.3 (RST), TP1.1 (1_1)
/base_mcu/RX_BLANK: J1.12 (IO8); also elsewhere on the board
/base_mcu/SCLK_MCU: J1.18 (IO12), R1.1
/base_mcu/TX_EN: J2.8 (IO40); also elsewhere on the board
GND: J1.22 (GND), J2.1 (GND), J2.21 (GND), J2.22 (GND), R8.2, R9.2, R10.2, TP2.1 (1_1); also elsewhere on the board
I2C_SCL: J2.5 (IO2), R4.2; also elsewhere on the board
I2C_SDA: J2.4 (IO1), R3.2; also elsewhere on the board
REF_CLK: J1.8 (IO15); also elsewhere on the board
SPI_MISO: J1.19 (IO13); also elsewhere on the board
SPI_MOSI: R2.2; also elsewhere on the board
SPI_SCLK: R1.2; also elsewhere on the board
TX_IFLAG_MCU: J1.6 (IO6); also elsewhere on the board
TX_TFLAG_MCU: J1.7 (IO7); also elsewhere on the board
VEXT_SENSE: J1.4 (IO4); also elsewhere on the board

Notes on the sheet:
Rail test points
TRIG_IO / TRIG_DIR
Block
DRV8871 field-cycling bridge
base
SPI2 on IO_MUX, 33 R at source
without a power_out driver
0/45/46, 3, 48
panel
ESP32-S3-DevKitC-1 /
DIO1-8, MOD OUT 1-7
OPA564 enable; polarizer FET
Net
CS_ADC / CS_DAC
P00-P07 -> 541; P10-P13/P15-P17 -> panel
Jinhua #40729, plugged in;
the USB-C ports face the
9 / 14
SPI_SCLK/MOSI/MISO
43 / 44
unused.
74LVC1T45 (1 = out to the SMA)
TX / C_SW
41 / 42
16 / 17
Function
receiver blanking switch
RX_BLANK
antenna u.FL -> pigtail ->
B1 / B3
I2C_SDA / I2C_SCL
IO0, IO45, IO46 = strapping (open); IO3 unused (v0.7)
400 kHz: 0x20, 0x60, 0x3C
1 / 2
4 x M3 mounting holes (4 mm from the corners) and 3 assembly fiducials
38 / 39
strapping / unused / PSRAM 35-37
rear / power edge.
OPTO_IN1 / 2
IO35-37 = octal PSRAM, IO48 = on-board RGB LED
